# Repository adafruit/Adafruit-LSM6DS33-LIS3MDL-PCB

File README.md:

## Adafruit LSM6DS33 + LIS3MDL 9-DoF IMU with Accel/Gyro/Mag PCB

<a href="http://www.adafruit.com/products/4485"><br/>
Click here to purchase one from the Adafruit shop</a>

PCB files for the Adafruit LSM6DS33 + LIS3MDL 9-DoF IMU with Accel/Gyro/Mag.

Format is EagleCAD schematic and board layout
* https://www.adafruit.com/product/4485

### Description

Add motion, direction and orientation sensing to your Arduino project with this all-in-one 9 Degree of Freedom (9-DoF) sensor with sensors from ST. This little breakout contains two chips that sit side-by-side to provide 9 degrees of full motion data.

The board includes an LSM6DS33, a 6-DoF IMU accelerometer + gyro. The 3-axis accelerometer, can tell you which direction is down towards the Earth (by measuring gravity) or how fast the board is accelerating in 3D space. The 3-axis gyroscope that can measure spin and twist. The three triple-axis sensors add up to 9 degrees of freedom.

It also includes a LIS3MDL 3-axis magnetometer that can sense where the strongest magnetic force is coming from, generally used to detect magnetic north. By combining this data you can orient the board.

These chips are not the newest motion sensors, but they are well-established and come at a great price. Together you have a nice 9 DoF IMU setup that is affordable for any project. Design your own activity or motion tracker with all the data...

To make getting started fast and easy, we placed the sensors on a compact breakout board with voltage regulation and level-shifted inputs. That way you can use them with 3V or 5V power/logic devices without worry. To make usage simple, we expose only the I2C interface and some interrupt pins from each chip. The breakout comes fully assembled and tested, with some extra header so you can use it on a breadboard. Four mounting holes make for a secure connection.

Additionally since it speaks I2C you can easily connect it up with two wires (plus power and ground!).  We've even included SparkFun qwiic compatible STEMMA QT connectors for the I2C bus so you don't even need to solder! Just wire up to your favorite micro like the STM32F405 Feather with a plug-and-play cable to get 9 DoF data ASAP. You can change the I2C addresses on the back using the solder jumpers, to have two of these sensor boards on one bus.

We also wrote libraries to help you get these sensors integrated with your Arduino/C++. This library covers the accel/gyro and this library is for the magnetometer. For advanced Arduino usage, ST has their own fully-featured library that includes extras such as FIFO management and tap detection for the LSM6DS3 and also for the LIS3MDL magnetometer

### License

Adafruit invests time and resources providing this open source design, please support Adafruit and open-source hardware by purchasing products from [Adafruit](https://www.adafruit.com)!

Designed by Limor Fried/Ladyada for Adafruit Industries.

Creative Commons Attribution/Share-Alike, all text above must be included in any redistribution.
See license.txt for additional details.

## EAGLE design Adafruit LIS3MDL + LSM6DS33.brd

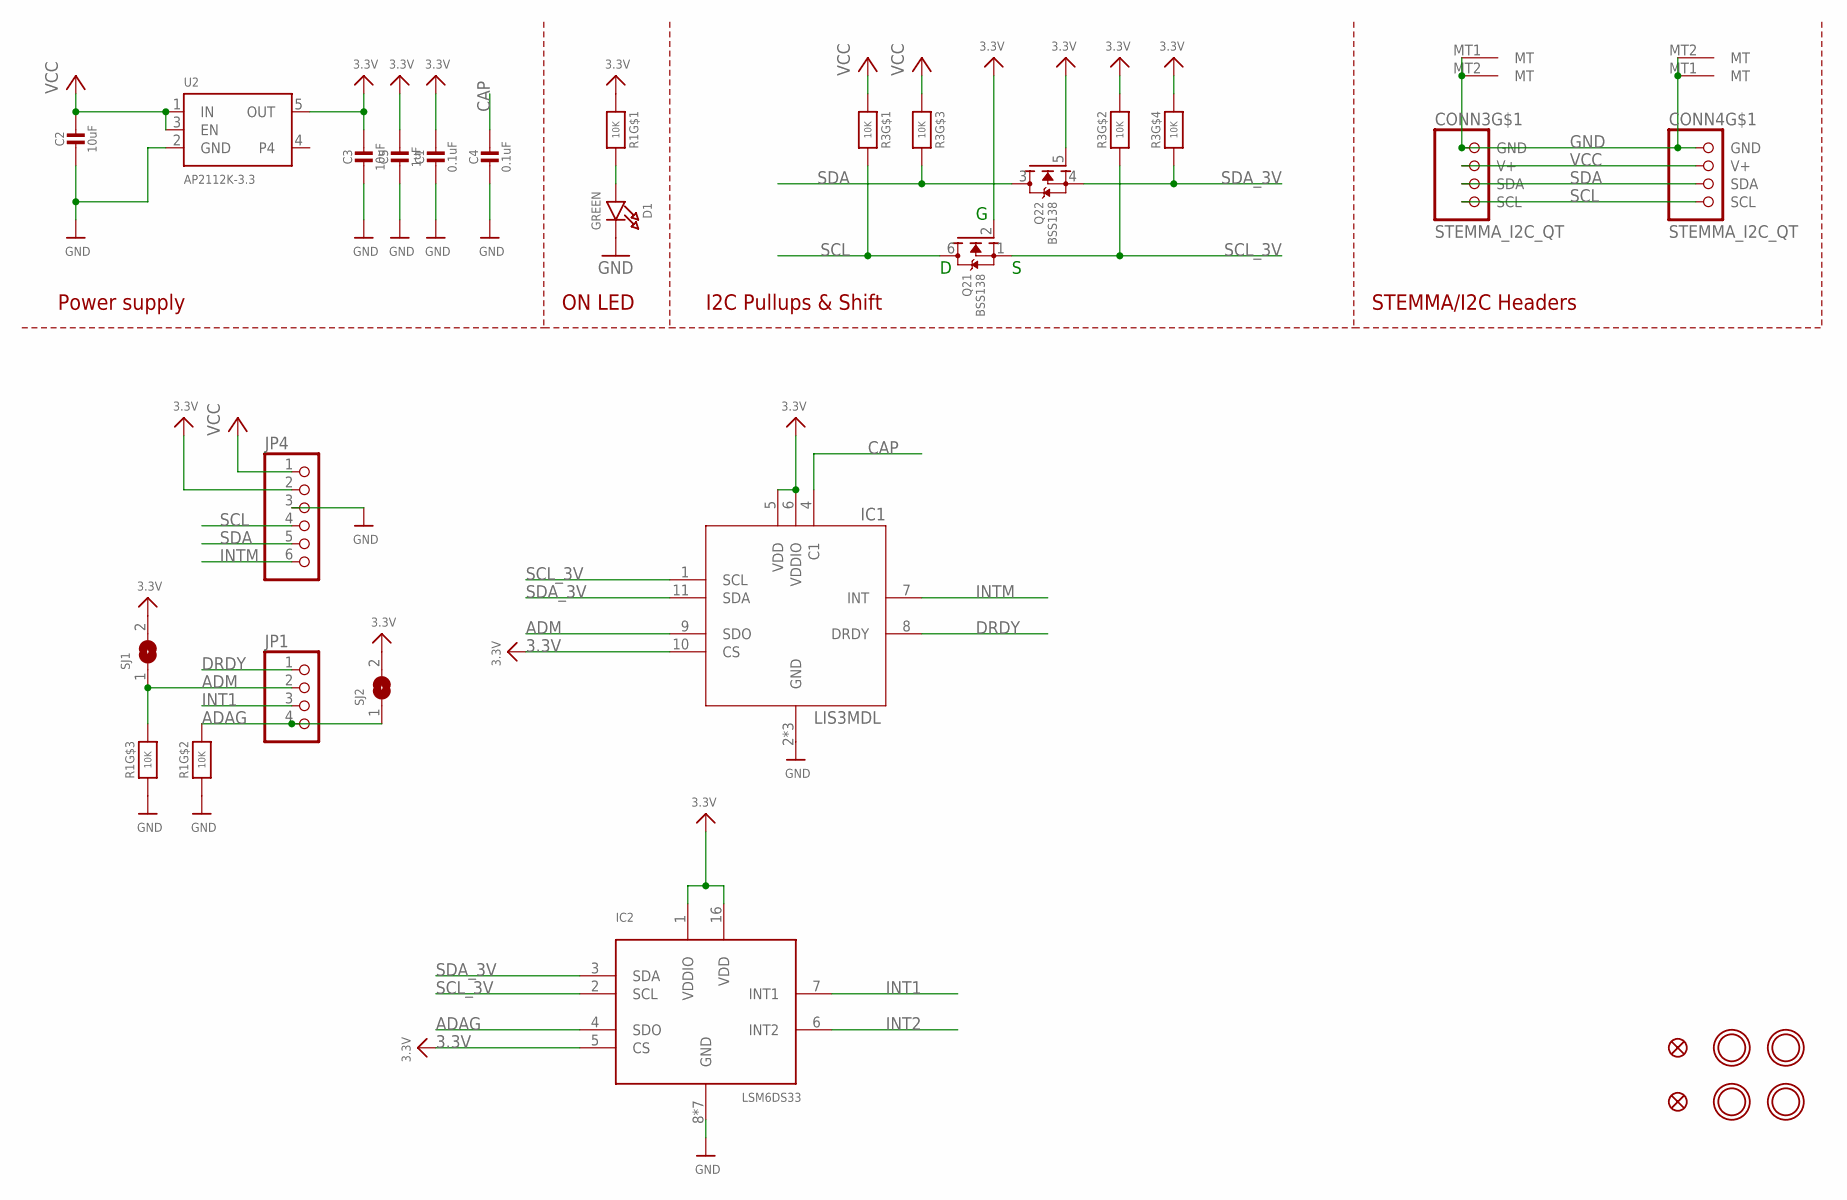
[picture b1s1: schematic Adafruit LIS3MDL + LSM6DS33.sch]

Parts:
C1, C4: 0.1uF; 0603-NO
C2, C3: 10uF; 0805-NO
C5: 1uF; 0603-NO
CONN3, CONN4: STEMMA_I2C_QT; JST_SH4
D1: GREEN; CHIPLED_0603_NOOUTLINE
FID3, FID4: FIDUCIAL_1MM
IC1: LIS3MDL; LGA12_2X2MM
IC2: LSM6DS33; LGA16_3X3MM
JP1: HEADER-1X4ROUND; 1X04_ROUND
JP4: HEADER-1X670MIL; 1X06_ROUND_70
Q2: BSS138; SOT363
R1, R3: 10K; RESPACK_4X0603
SJ1, SJ2: SOLDERJUMPER; SOLDERJUMPER_ARROW_NOPASTE
U2: AP2112K-3.3; SOT23-5
U$1, U$17, U$19, U$21: MOUNTINGHOLE2.5; MOUNTINGHOLE_2.5_PLATED

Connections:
3.3V: C1.1, C3.1, C5.1, IC1.5 (VDD), IC1.6 (VDDIO), IC1.10 (CS), IC2.1 (VDDIO), IC2.5 (CS), IC2.16 (VDD), JP4.2, Q2.2 (G), Q2.5 (G), R1.1, R3.2 (1), R3.4 (1), SJ1.2, SJ2.2, U2.5 (OUT)
ADAG: IC2.4 (SDO), JP1.4, R1.7 (2), SJ2.1
ADM: IC1.9 (SDO), JP1.2, R1.6 (2), SJ1.1
CAP: C4.1, IC1.4 (C1)
DRDY: IC1.8 (DRDY), JP1.1
GND: C1.2, C2.2, C3.2, C4.2, C5.2, CONN3.1 (GND), CONN3.MT1 (MT), CONN3.MT2 (MT), CONN4.1 (GND), CONN4.MT1 (MT), CONN4.MT2 (MT), D1.C, IC1.2 (GND), IC1.3 (GND), IC1.12 (GND), IC2.8 (GND), IC2.9 (GND), IC2.10 (GND), IC2.11 (GND), IC2.12 (GND), IC2.13 (GND), IC2.15 (GND), JP4.3, R1.2 (1), R1.3 (1), U2.2 (GND)
INT1: IC2.7 (INT1), JP1.3
INT2: IC2.6 (INT2)
INTM: IC1.7 (INT), JP4.6
unnamed: D1.A, R1.8 (2)
SCL: CONN3.4 (SCL), CONN4.4 (SCL), JP4.4, Q2.6 (D), R3.8 (2)
SCL_3V: IC1.1 (SCL), IC2.2 (SCL), Q2.1 (S), R3.7 (2)
SDA: CONN3.3 (SDA), CONN4.3 (SDA), JP4.5, Q2.3 (D), R3.6 (2)
SDA_3V: IC1.11 (SDA), IC2.3 (SDA), Q2.4 (S), R3.5 (2)
VCC: C2.1, CONN3.2 (V+), CONN4.2 (V+), JP4.1, R3.1, R3.3 (1), U2.1 (IN), U2.3 (EN)

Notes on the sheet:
I2C Pullups & Shift
STEMMA/I2C Headers
ON LED
Power supply

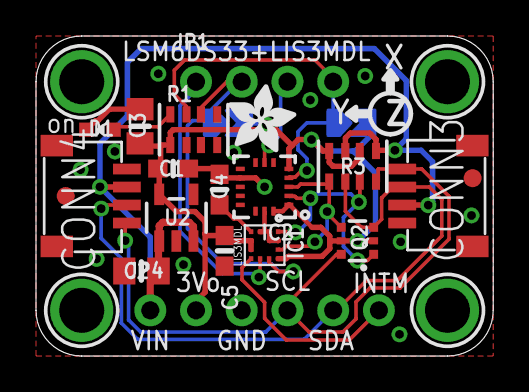
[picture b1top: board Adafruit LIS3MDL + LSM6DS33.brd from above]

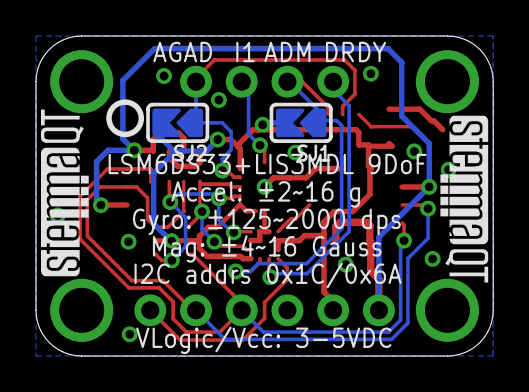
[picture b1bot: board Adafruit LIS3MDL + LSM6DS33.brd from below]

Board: 2 copper layers, 25.4 x 17.8 mm, 28 parts (5 on the bottom side), 14 nets.

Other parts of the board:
U$20: ADAFRUIT_3.5MM
U$25: PCBFEAT-REV-040
U$30, U$31: STEMMAQT

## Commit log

2020-06-10 Adding board files.

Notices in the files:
parts and their libraries:
microbuilder: This work is placed in the public domain, and may be freely used for commercial and non-commercial work with the following conditions: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
